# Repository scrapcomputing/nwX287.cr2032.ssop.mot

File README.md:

# CR2032 SSOP MOT version of Necroware's nwX287 RTC module

This is a modified version of Necroware's nwX287 RTC module with the following features:
- It uses a common through-hole CR2032 battery holder instead of a CR1225
- It works with an SSOP-24 RTC IC
- It includes a solder-pad for selecting Intel or Motorola bus mode.

For detailed information about the project, please refer to Necroware's original page: https://github.com/necroware/nwX287

## Videos
- Building this module: https://www.youtube.com/watch?v=k7J6g3XWbXA
- Necroware's original video: https://www.youtube.com/watch?v=svPNxILeQEw

## J1 Intel/Motorola mode for BQ3285
BQ3285 Pin 1 is labeled as `MOT` and selects the bus type: Intel or Motorola.
If not set, it defaults to Intel.
BQ4285 uses this pin for providing external power.

The latest `.mot` revision of the board features a solder jumper that connects this Pin 1 of the Timer chip to either pin 1 of the socket or to Vcc.
- For Intel mode or if using BQ4285, short pins 1-2.
- For Motorola mode with the BQ3285, short pins 2-3.

## Bill of Materials

Gerber files are published in the releases: https://github.com/scrapcomputing/nwX287.cr2032.ssop.mot/releases

Part | # | Description
-----|---|-----------------------------------------
U1   | 1 | Real-Time Clock BQ3285S or BQ4285S SSOP-24
Y1   | 1 | Crystal oscillator 32.768kHz 6pF
BT1  | 1 | CR2032 through-hole battery holder

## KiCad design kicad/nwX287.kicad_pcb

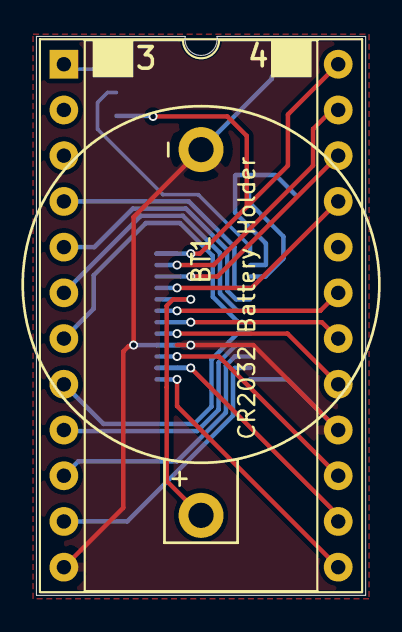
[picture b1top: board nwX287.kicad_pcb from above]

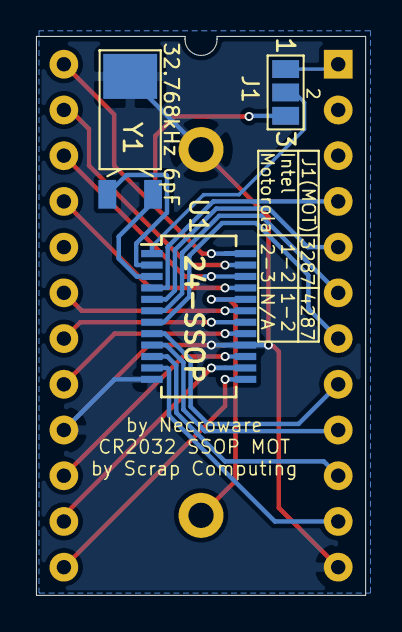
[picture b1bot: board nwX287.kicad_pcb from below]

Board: 2 copper layers, 18.3 x 31.1 mm, 5 parts (3 on the bottom side), 24 nets.

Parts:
BT1: CR2032; CR2032_battery_holder
J1: Conn_01x03_Male; SolderJumper-3_P1.3mm_Open_Pad1.0x1.5mm_NumberLabels
U1: bq4285; SSOP-24_3.9x8.7mm_P0.635mm
U2: socket; DIP-24_W15.24mm_Socket
Y1: 32.768kHz 6pF; Crystal_SMD_FrontierElectronics_FM206

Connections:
AD0: U1.4, U2.4
AD1: U1.5, U2.5
AD2: U1.6, U2.6
AD3: U1.7, U2.7
AD4: U1.8, U2.8
AD5: U1.9, U2.9
AD6: U1.10, U2.10
AD7: U1.11, U2.11
AS: U1.14, U2.14
BC: BT1.1, U1.20
CEI: U1.21, U2.21
CEO: U1.22, U2.22
CS: U1.13, U2.13
DS: U1.17, U2.17
GND: BT1.2, U1.12, U1.16, U2.12, U2.16, Y1.3
INT: U1.19, U2.19
unnamed: J1.2, U1.1
RST: U1.18, U2.18
RW: U1.15, U2.15
SQW: U1.23, U2.23
VCC: J1.3, U1.24, U2.24
VOUT: J1.1, U2.1
X1: U1.2, Y1.2
X2: U1.3, Y1.1

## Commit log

2023-07-23 CR2032, SSOP-24 and MOT
2023-10-21 Update README with the youtube video.
